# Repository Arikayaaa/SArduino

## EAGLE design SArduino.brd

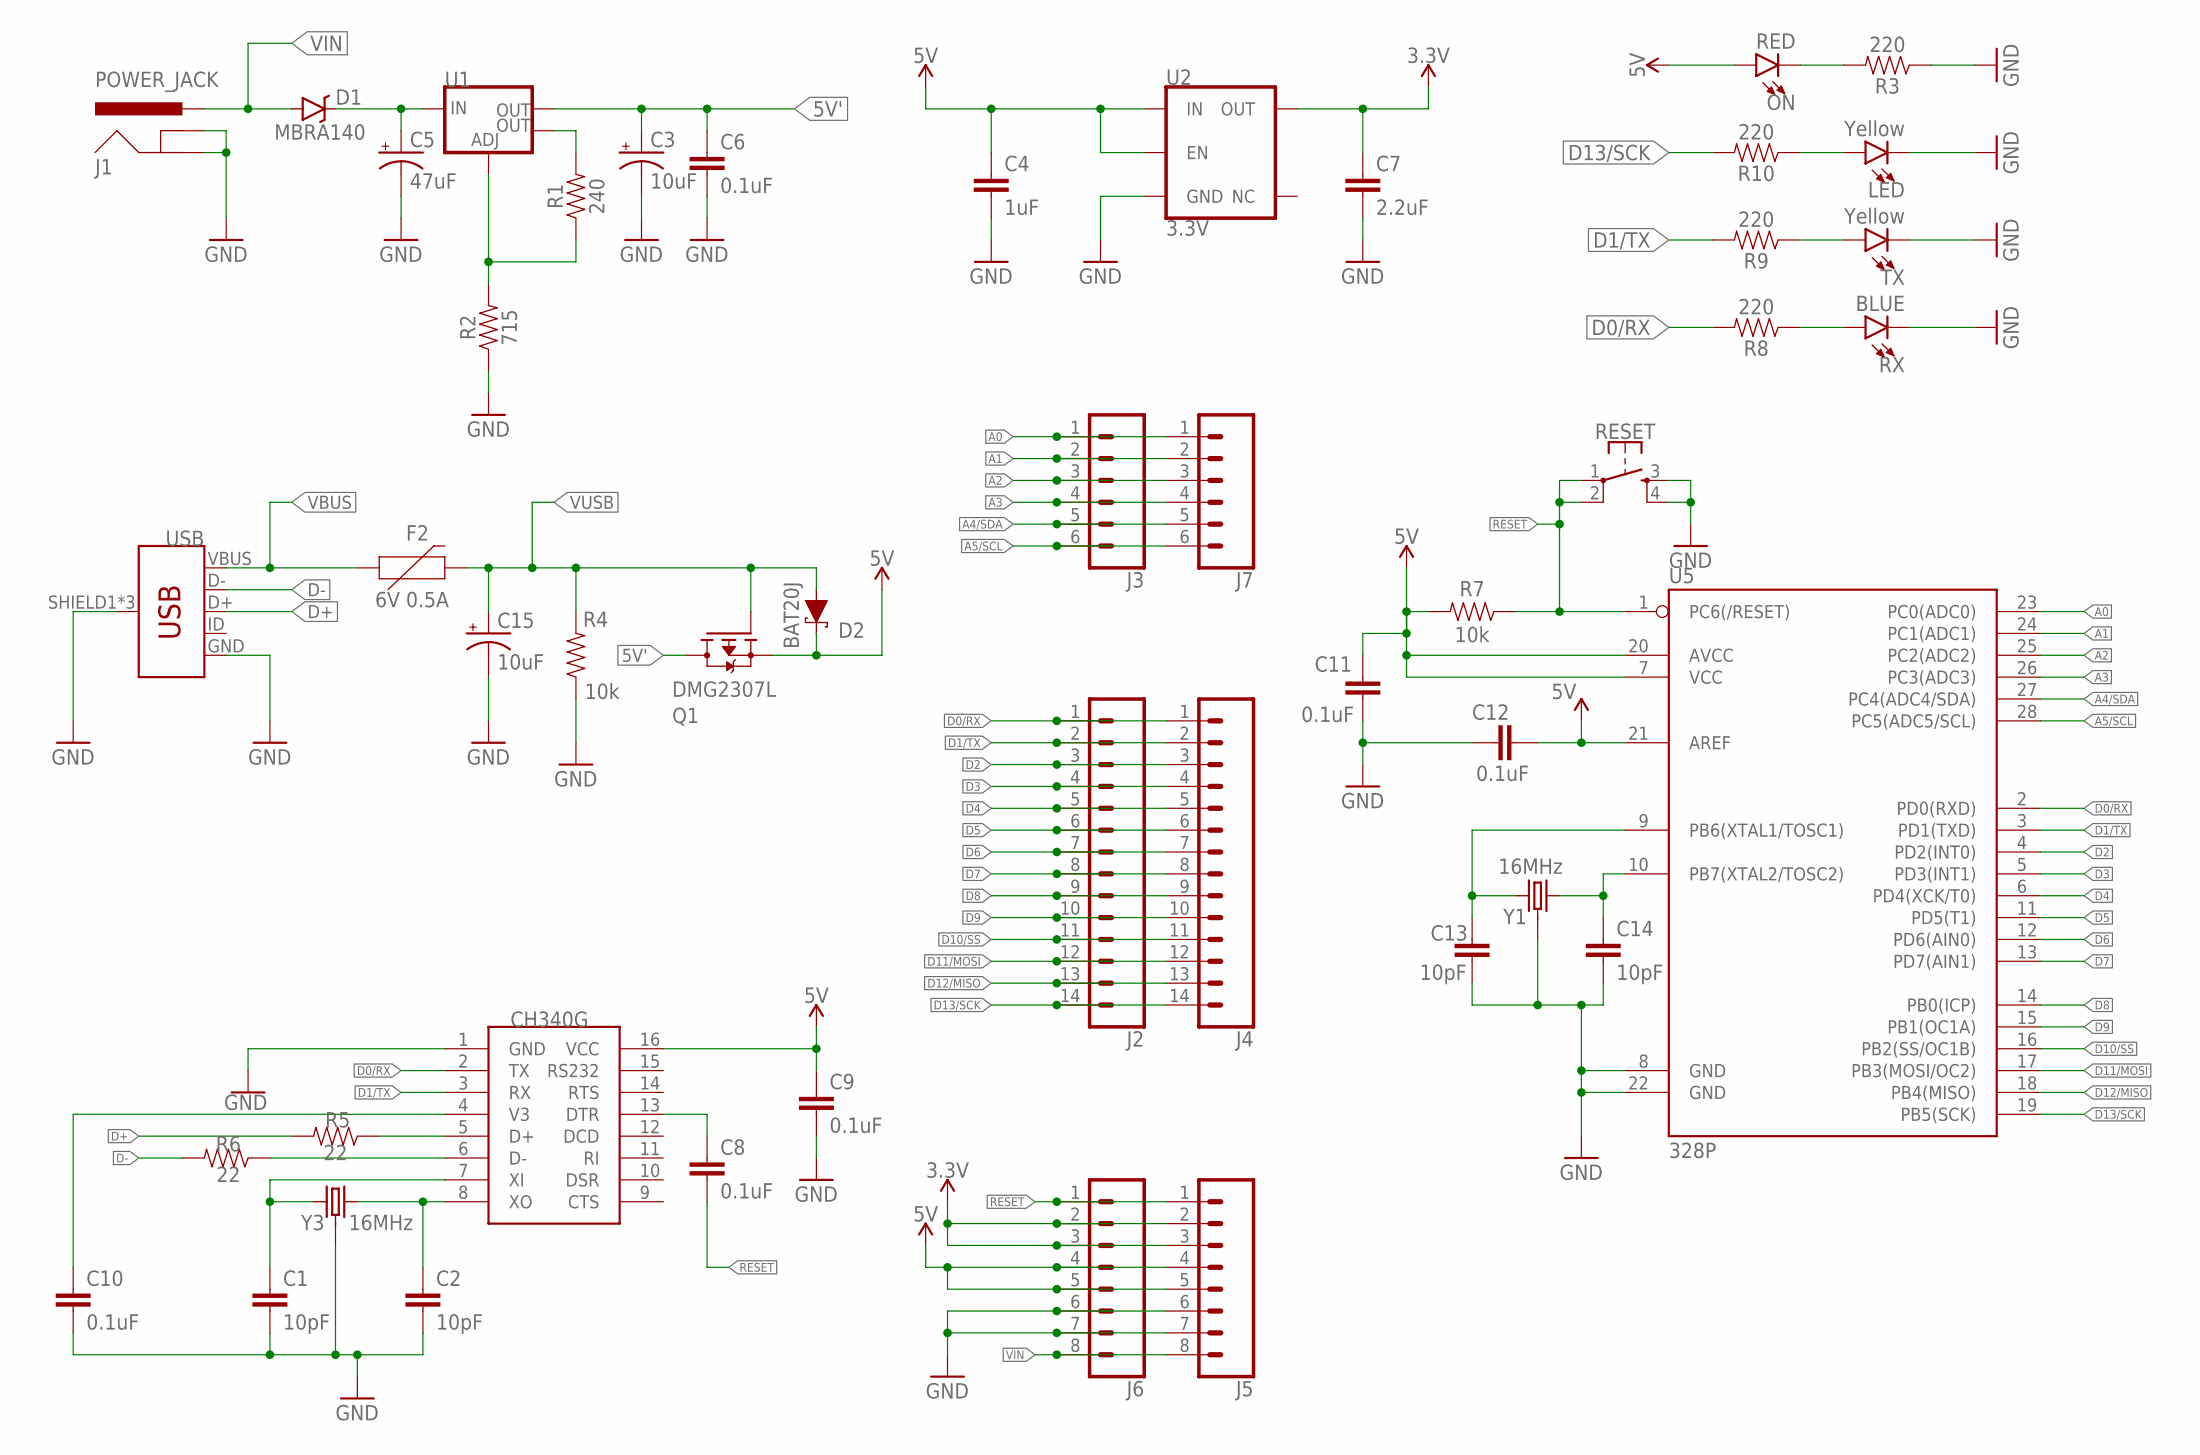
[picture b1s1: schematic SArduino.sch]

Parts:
C1, C2, C13, C14: 10pF; 0603
C3, C15: 10uF; EIA3216
C4: 1uF; 0603
C5: 47uF; PANASONIC_D
C6, C8, C9, C10, C11, C12: 0.1uF; 0603
C7: 2.2uF; 0603
D1: MBRA140; SMA-DIODE@1
D2: BAT20J; SOD-323
F2: 6V 0.5A; 0805
J1: POWER_JACK; POWER_JACK_PTH
J2, J4: CONN_14; 1X14
J3, J7: CONN_06SILK_FEMALE_PTH; 1X06
J5, J6: CONN_08"; 1X08
LED: Yellow; LED-0603
ON: RED; LED-0603
Q1: DMG2307L; SOT96P240X110-3N
R1: 240; 0603
R2: 715; 0603
R3, R8, R9, R10: 220; 0603
R4, R7: 10k; 0603
R5, R6: 22; 0603
RESET: MOMENTARY-SWITCH-SPST-2-SMD-5.2MM; TACTILE_SWITCH_SMD_5.2MM
RX: BLUE; LED-0603
TX: Yellow; LED-0603
U1: V_REG_LM1117SOT223; SOT223
U2: 3.3V; SOT23-5
U3: CH340G; SOIC16
U5: 328P; DIP28
USB: USB_MICRO-B_FEMALE-SMT; USB-B-MICRO-SMD
Y1, Y3: 16MHz; CRYSTAL-SMD-3.2X2.5MM

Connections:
3.3V: C7.1, J5.2, J5.3, J6.2, J6.3, U2.5 (OUT)
5V: C4.1, C9.1, C11.2, C12.2, D2.C, J5.4, J5.5, J6.4, J6.5, ON.A, Q1.2 (S), R7.2, U2.1 (IN), U2.3 (EN), U3.16 (VCC), U5.7 (VCC), U5.20 (AVCC), U5.21 (AREF)
5V': C3.+, C6.1, Q1.3 (D), U1.2 (OUT)
A0: J3.1, J7.1, U5.23 (PC0(ADC0))
A1: J3.2, J7.2, U5.24 (PC1(ADC1))
A2: J3.3, J7.3, U5.25 (PC2(ADC2))
A3: J3.4, J7.4, U5.26 (PC3(ADC3))
A4/SDA: J3.5, J7.5, U5.27 (PC4(ADC4/SDA))
A5/SCL: J3.6, J7.6, U5.28 (PC5(ADC5/SCL))
D0/RX: J2.1, J4.1, R8.2, U3.2 (TX), U5.2 (PD0(RXD))
D1/TX: J2.2, J4.2, R9.2, U3.3 (RX), U5.3 (PD1(TXD))
D2: J2.3, J4.3, U5.4 (PD2(INT0))
D3: J2.4, J4.4, U5.5 (PD3(INT1))
D4: J2.5, J4.5, U5.6 (PD4(XCK/T0))
D5: J2.6, J4.6, U5.11 (PD5(T1))
D6: J2.7, J4.7, U5.12 (PD6(AIN0))
D7: J2.8, J4.8, U5.13 (PD7(AIN1))
D8: J2.9, J4.9, U5.14 (PB0(ICP))
D9: J2.10, J4.10, U5.15 (PB1(OC1A))
D10/SS: J2.11, J4.11, U5.16 (PB2(SS/OC1B))
D11/MOSI: J2.12, J4.12, U5.17 (PB3(MOSI/OC2))
D12/MISO: J2.13, J4.13, U5.18 (PB4(MISO))
D13/SCK: J2.14, J4.14, R10.2, U5.19 (PB5(SCK))
D+: R5.2, USB.D+
D-: R6.2, USB.D-
GND: C1.2, C2.2, C3.-, C4.2, C5.-, C6.2, C7.2, C9.2, C10.2, C11.1, C12.1, C13.2, C14.2, C15.-, J1.GND, J1.GNDBREAK, J5.6, J5.7, J6.6, J6.7, LED.C, R2.1, R3.1, R4.1, RESET.3, RESET.4, RX.C, TX.C, U2.2 (GND), U3.1 (GND), U5.8 (GND), U5.22 (GND), USB.GND, USB.SHIELD1 (SHIELD), USB.SHIELD2 (SHIELD), USB.SHIELD3 (SHIELD), Y1.2 (GND), Y1.4 (GND), Y3.2 (GND), Y3.4 (GND)
unnamed: C5.+, D1.C, U1.3 (IN)
unnamed: ON.C, R3.2
unnamed: R8.1, RX.A
unnamed: R9.1, TX.A
unnamed: LED.A, R10.1
unnamed: R5.1, U3.5 (D+)
unnamed: R6.1, U3.6 (D-)
unnamed: C2.1, U3.8 (XO), Y3.3 (2)
unnamed: C13.1, U5.9 (PB6(XTAL1/TOSC1)), Y1.1
unnamed: C1.1, U3.7 (XI), Y3.1
unnamed: C10.1, U3.4 (V3)
unnamed: C14.1, U5.10 (PB7(XTAL2/TOSC2)), Y1.3 (2)
unnamed: R1.2, U1.4 (OUT)
unnamed: R1.1, R2.2, U1.1 (ADJ)
unnamed: C8.1, U3.13 (DTR)
RESET: C8.2, J5.1, J6.1, R7.1, RESET.1, RESET.2, U5.1 (PC6(/RESET))
VBUS: F2.1, USB.VBUS
VIN: D1.A, J1.PWR, J5.8, J6.8
VUSB: C15.+, D2.A, F2.2, Q1.1 (G), R4.2

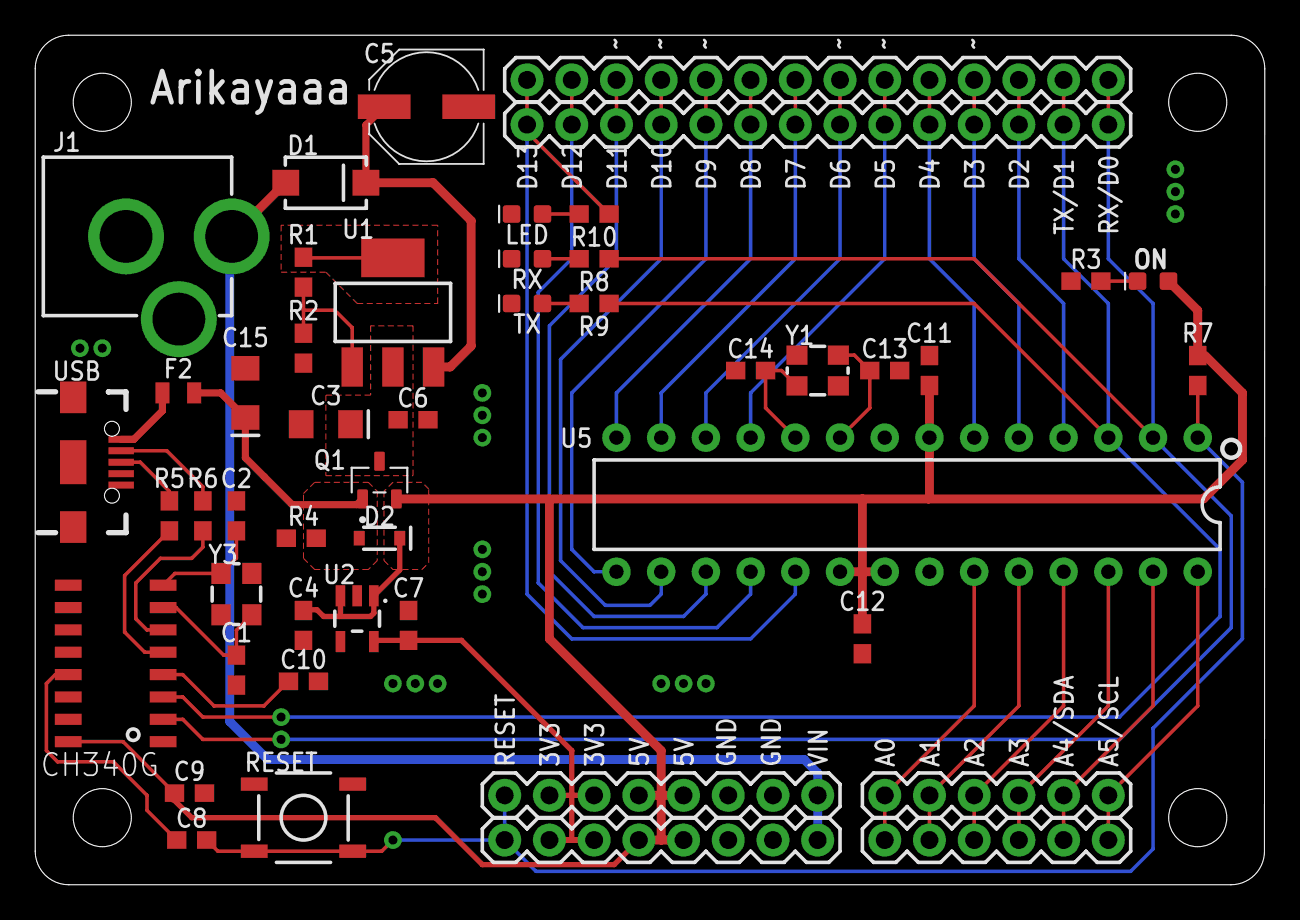
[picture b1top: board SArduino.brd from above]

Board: 2 copper layers, 69.8 x 48.3 mm, 48 parts (0 on the bottom side), 45 nets.

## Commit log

2022-05-09 Gerber files was added
2022-05-09 Revert "Merge branch 'master' of https://github.com/Arikayaaa/SArduino"
    This reverts commit 15fa3a1b2c133cafb03e0620b7a7a7ce919d822d, reversing
    changes made to 0dc47b68ebb76eaf9a5c94a9a2bdb2520f0b0320.

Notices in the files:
parts and their libraries:
SparkFun-Capacitors: Licensing: CC v3.0 Share-Alike You are welcome to use this library for commercial purposes.
SparkFun-DiscreteSemi: Licensing: Creative Commons ShareAlike 4.0 International - https://creativecommons.org/licenses/by-sa/4.0
